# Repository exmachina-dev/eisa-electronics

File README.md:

```
____ _ ____ _    ____    ____ _    ____ ____ ___ ____ ____ _  _ _ ____ ____ 
|___ | [__  |    |__| __ |___ |    |___ |     |  |__/ |  | |\ | | |    [__  
|___ | ___] |___ |  |    |___ |___ |___ |___  |  |  \ |__| | \| | |___ ___] 
 
```

# Eisla electronics

This repo contains all necessary files to design and produce PCBs for the Eisla product range.

## File format and folder structure

Documentation files should be in PDF. Board image files can be in PNG or PDF.

PCB design files are in EAGLE Standard edition (7.4) file format.

The following are general rules to help maintain a consistent folder structure:

* All libraries are placed inside the shared libraries repository. It can be found
  on [Github](https://github.com/exmchina-dev/eagle-resources)

* One board for each project folder.  

* Mutiples revisions can be placed inside a subfolder. i.e. `ArmazCape/Rev A1`

* BOMs, partlists, spreadsheet should placed inside a `BOMs/` folder.  

* Documentations files are in `doc/` inside a project folder.

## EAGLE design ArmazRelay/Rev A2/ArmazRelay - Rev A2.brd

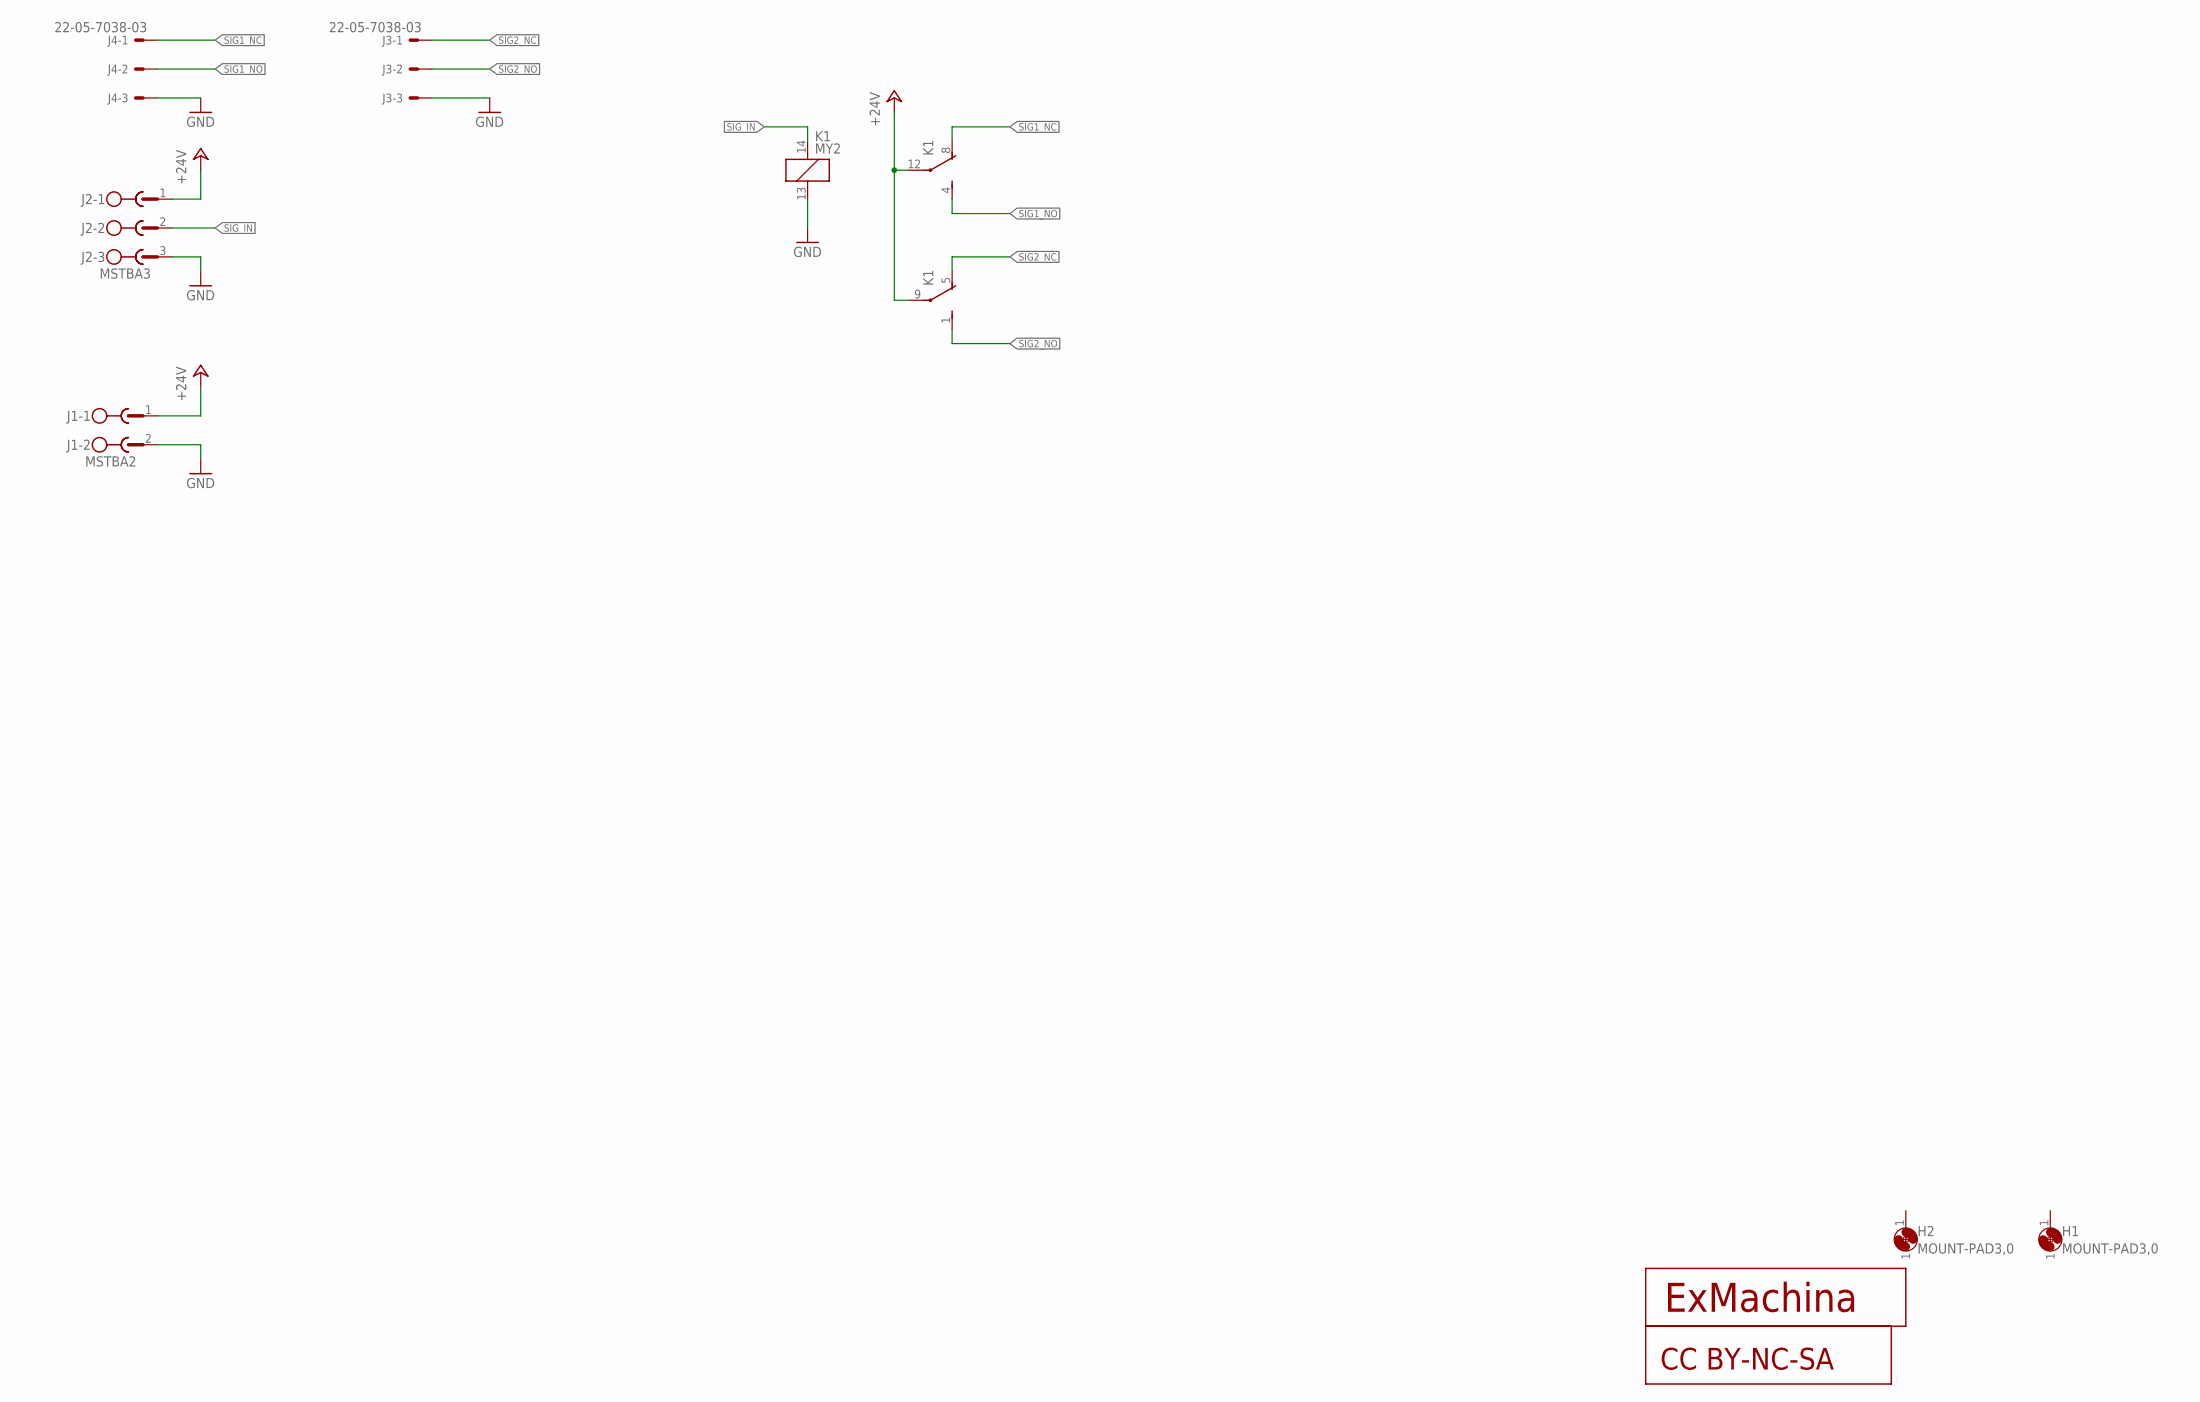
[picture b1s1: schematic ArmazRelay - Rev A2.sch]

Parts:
CC1: CC-BY-NC-SA
H1, H2: MOUNT-PAD3,0; P3,0
J1: MSTBA2
J2: MSTBA3
J3, J4: 22-05-7038-03; 7395-03
K1: MY2; PY08
T1: EXMACHINA-LOGO-NAME; EXM-LOGO-BASELINE

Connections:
+24V: J1.1, J2.1, K1.9 (C), K1.12 (C)
GND: J1.2, J2.3, J3.3, J4.3, K1.13 (COIL2)
SIG1_NC: J4.1, K1.8 (NO)
SIG1_NO: J4.2, K1.4 (NC)
SIG2_NC: J3.1, K1.5 (NO)
SIG2_NO: J3.2, K1.1 (NC)
SIG_IN: J2.2, K1.14 (COIL1)

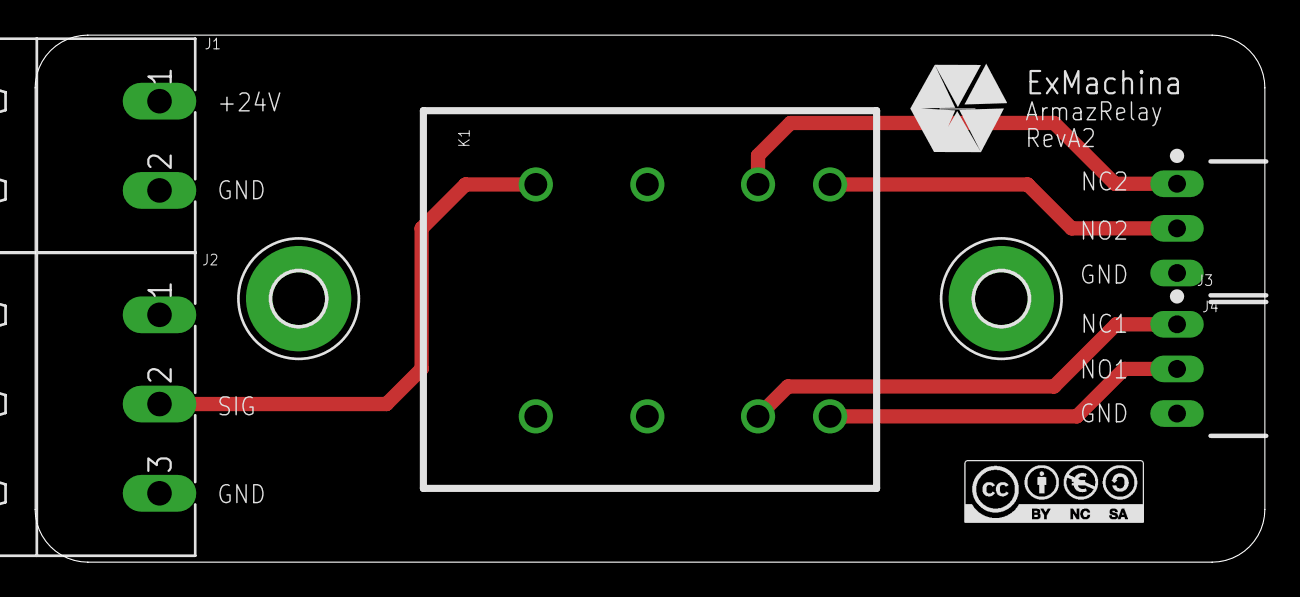
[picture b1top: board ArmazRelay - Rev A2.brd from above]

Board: 2 copper layers, 70.0 x 30.0 mm, 10 parts (0 on the bottom side), 7 nets.

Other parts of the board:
U$1: A4L-LOC

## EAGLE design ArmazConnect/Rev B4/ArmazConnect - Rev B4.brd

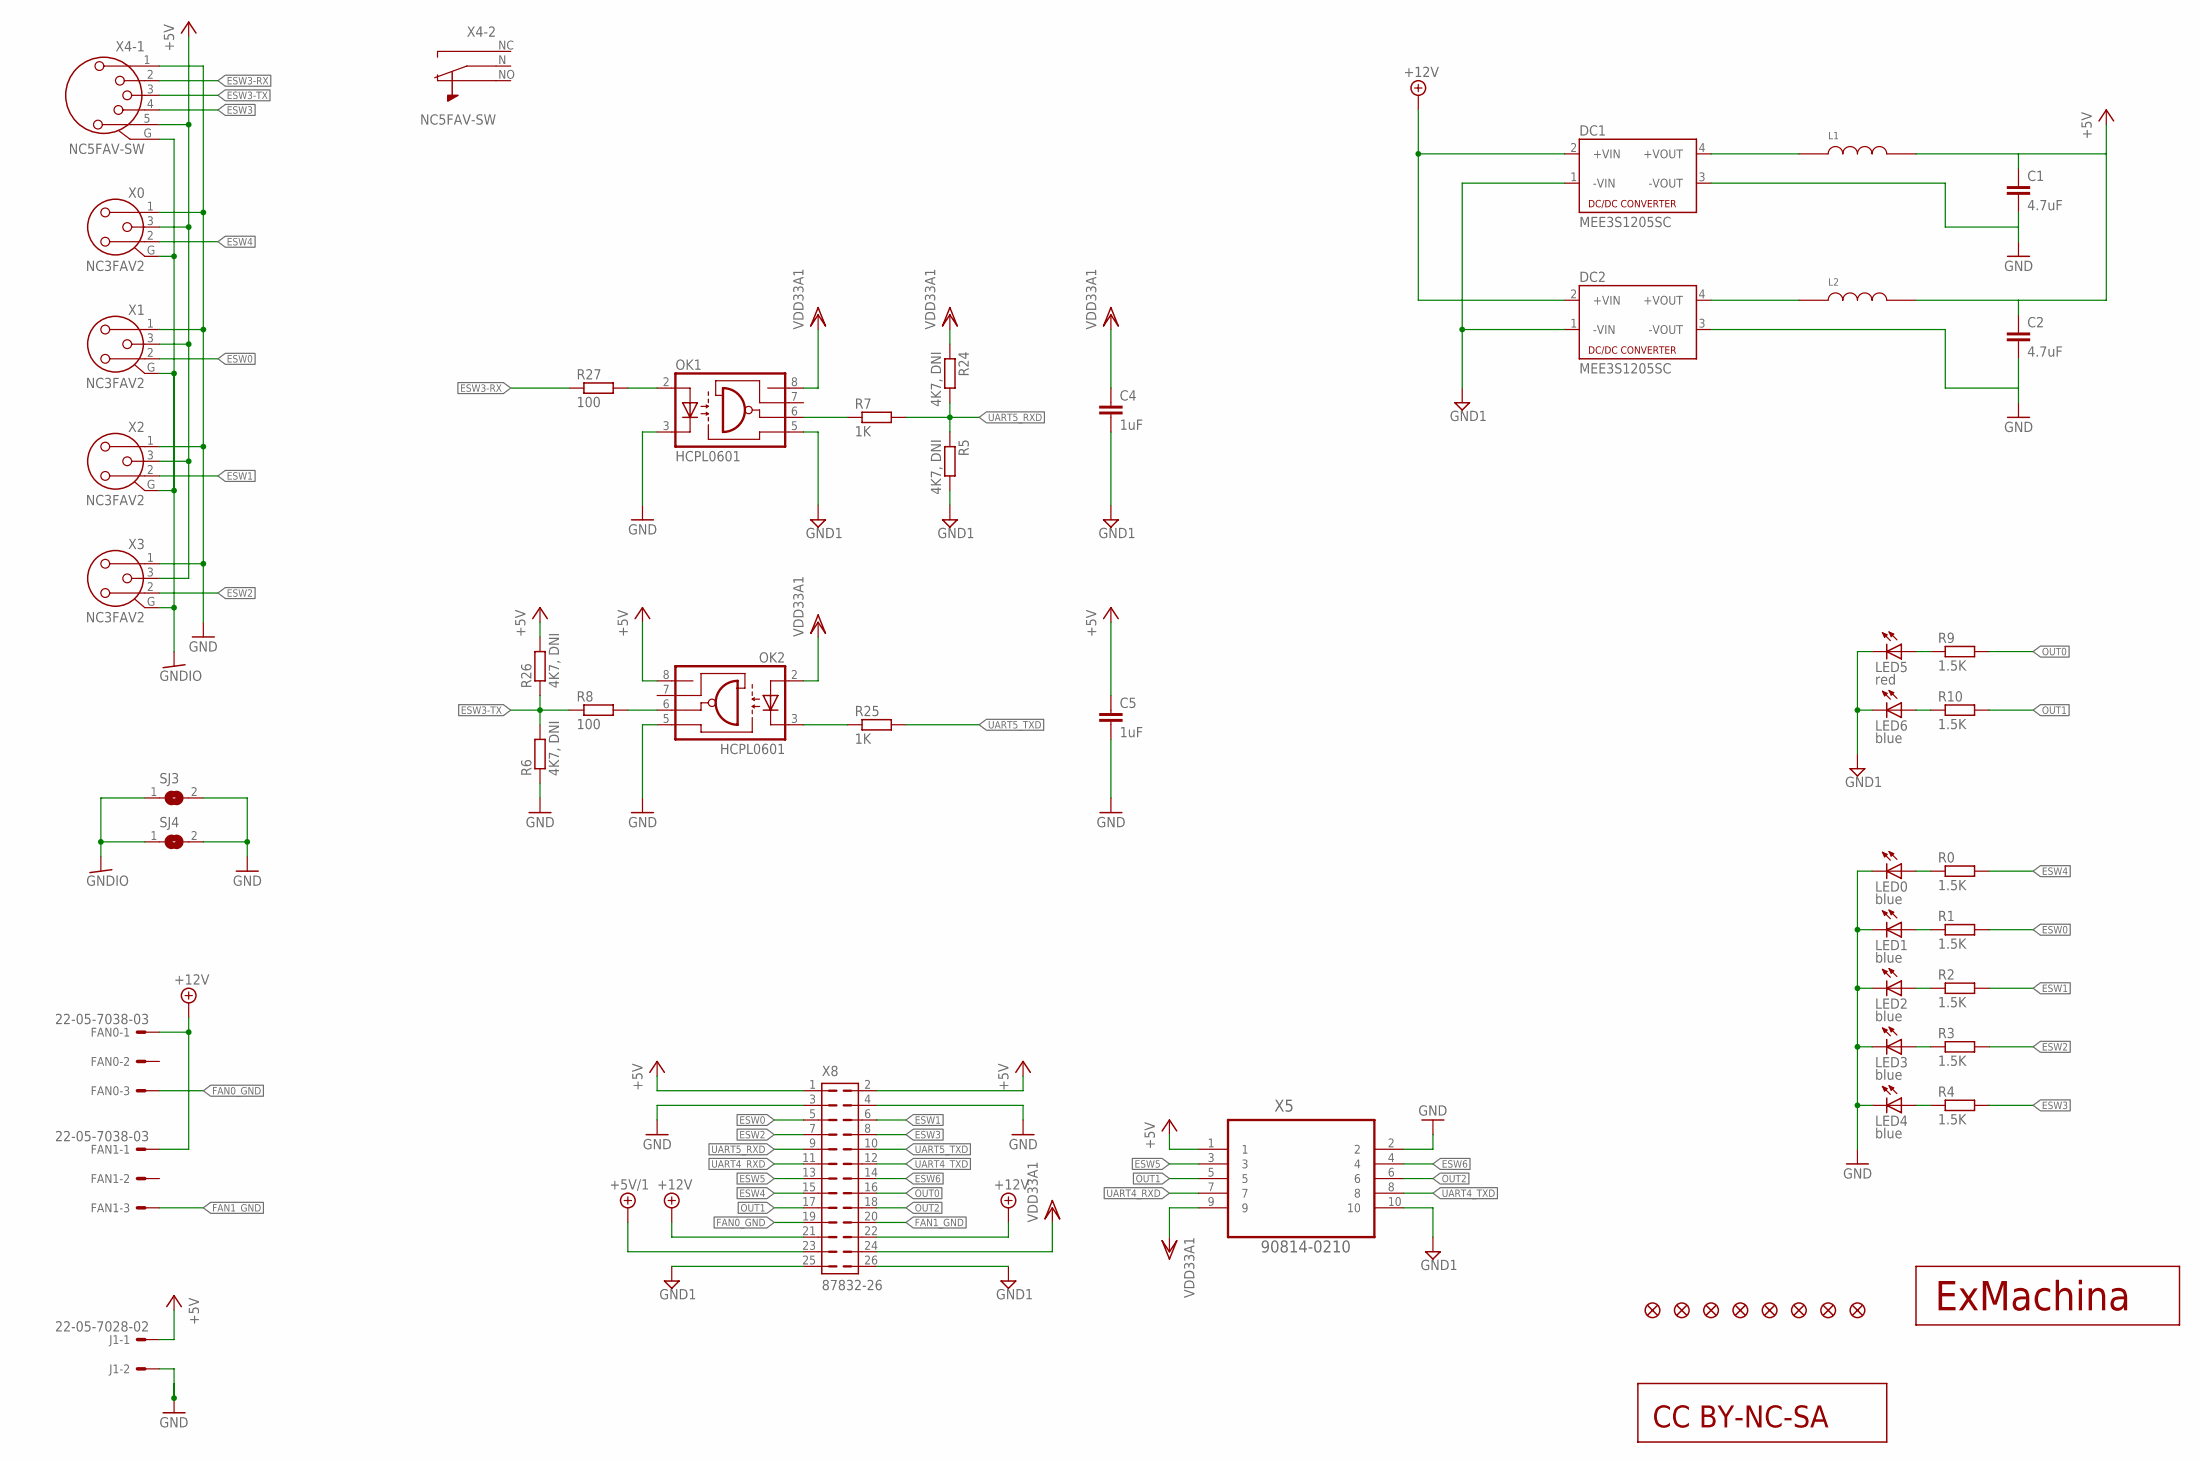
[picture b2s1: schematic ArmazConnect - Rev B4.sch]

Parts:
C1, C2: 4.7uF; C0603; MPN MC0603X475K6R3CT
C4, C5: 1uF; C0805; MPN MC0805F105Z500CT
CC1: CC-BY-NC-SA
DC1, DC2: MEE3S1205SC; MEE3; MPN MEE3S1205SC
FAN0, FAN1: 22-05-7038-03; 7395-03; MPN 22-05-7038
FI1, FI2, FI3, FI4, FI5, FI6, FI7, FI8: FIDUCIAL1X2; FIDUCIAL-1X2
J1: 22-05-7028-02; 7395-02
L1, L2: 84103C; 8200; MPN 744045100
LED0, LED1, LED2, LED3, LED4, LED6: blue; CHIP-LED0603; MPN OVS-0603
LED5: red; CHIP-LED0603; MPN OVS-0603
OK1, OK2: HCPL0601; SOIC08
R0, R1, R2, R3, R4, R9, R10: 1.5K; R0603; MPN MCMR06X1501FTL
R5, R6, R24, R26: 4K7, DNI; R0603; MPN MCMR04X3301FTL
R7, R25: 1K; R0603; MPN MCMR06X3300FTL
R8, R27: 100; R0603; MPN MCMR06X4701FTL
SJ3, SJ4: SJ
U$1: EXMACHINA-LOGO-NAME; EXM-LOGO-BASELINE
X0, X1, X2, X3: NC3FAV2; MPN NC3FAAV2
X4: NC5FAV-SW
X5: 90814-0210; MOLEX_90814-0210
X8: 87832-26; MPN 87832-2620

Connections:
+5V: C1.1, C2.1, C5.1, J1.1, L1.2, L2.2, OK2.8 (VCC), R26.2, X0.3, X1.3, X2.3, X3.3, X4.5, X5.1, X8.1, X8.2
+5V/1: X8.23
+12V: DC1.2 (+VIN), DC2.2 (+VIN), FAN0.1, FAN1.1, X8.21, X8.22
ESW0: R1.2, X1.2, X8.5
ESW1: R2.2, X2.2, X8.6
ESW2: R3.2, X3.2, X8.7
ESW3: R4.2, X4.4, X8.8
ESW3-RX: R27.1, X4.2
ESW3-TX: R6.2, R8.1, R26.1, X4.3
ESW4: R0.2, X0.2, X8.15
ESW5: X5.3, X8.13
ESW6: X5.4, X8.14
FAN0_GND: FAN0.3, X8.19
FAN1_GND: FAN1.3, X8.20
GND: C1.2, C2.2, C5.2, DC1.3 (-VOUT), DC2.3 (-VOUT), J1.2, LED0.C, LED1.C, LED2.C, LED3.C, LED4.C, OK1.3 (C), OK2.5 (GND), R6.1, SJ3.2, SJ4.2, X0.1, X1.1, X2.1, X3.1, X4.1, X5.2, X8.3, X8.4
GND1: C4.2, DC1.1 (-VIN), DC2.1 (-VIN), LED5.C, LED6.C, OK1.5 (GND), R5.2, X5.10, X8.25, X8.26
GNDIO: SJ3.1, SJ4.1, X0.G, X1.G, X2.G, X3.G, X4.G
unnamed: LED1.A, R1.1
unnamed: LED2.A, R2.1
unnamed: LED3.A, R3.1
unnamed: LED4.A, R4.1
unnamed: DC1.4 (+VOUT), L1.1
unnamed: OK1.2 (A), R27.2
unnamed: DC2.4 (+VOUT), L2.1
unnamed: OK2.6 (VO), R8.2
unnamed: LED5.A, R9.1
unnamed: OK1.6 (VO), R7.1
unnamed: LED6.A, R10.1
unnamed: LED0.A, R0.1
unnamed: OK2.3 (C), R25.1
OUT0: R9.2, X8.16
OUT1: R10.2, X5.5, X8.17
OUT2: X5.6, X8.18
UART4_RXD: X5.7, X8.11
UART4_TXD: X5.8, X8.12
UART5_RXD: R5.1, R7.2, R24.2, X8.9
UART5_TXD: R25.2, X8.10
VDD33A1: C4.1, OK1.8 (VCC), OK2.2 (A), R24.1, X5.9, X8.24

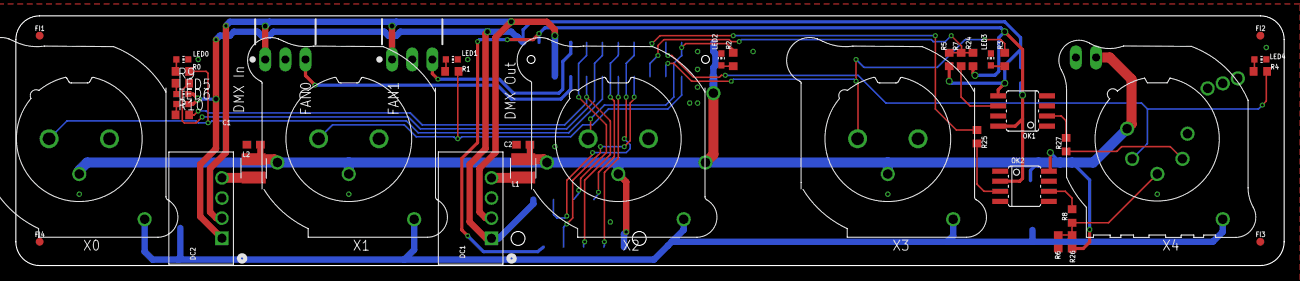
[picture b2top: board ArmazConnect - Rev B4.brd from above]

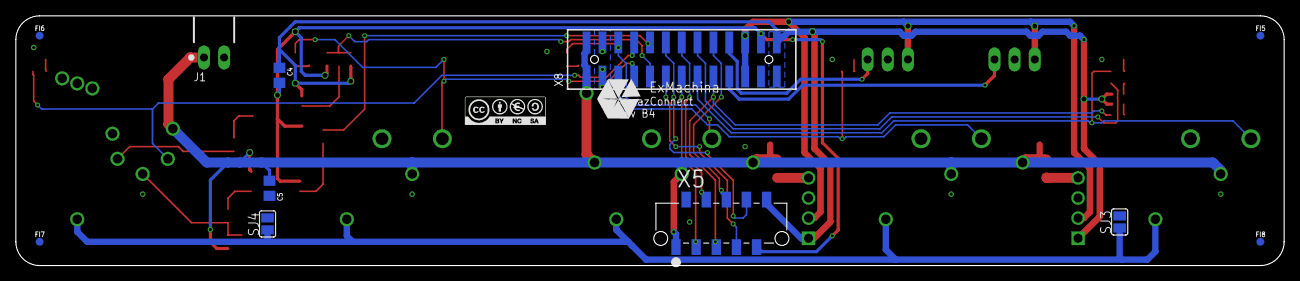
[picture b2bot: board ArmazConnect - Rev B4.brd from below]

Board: 2 copper layers, 160.0 x 31.5 mm, 54 parts (13 on the bottom side), 37 nets.

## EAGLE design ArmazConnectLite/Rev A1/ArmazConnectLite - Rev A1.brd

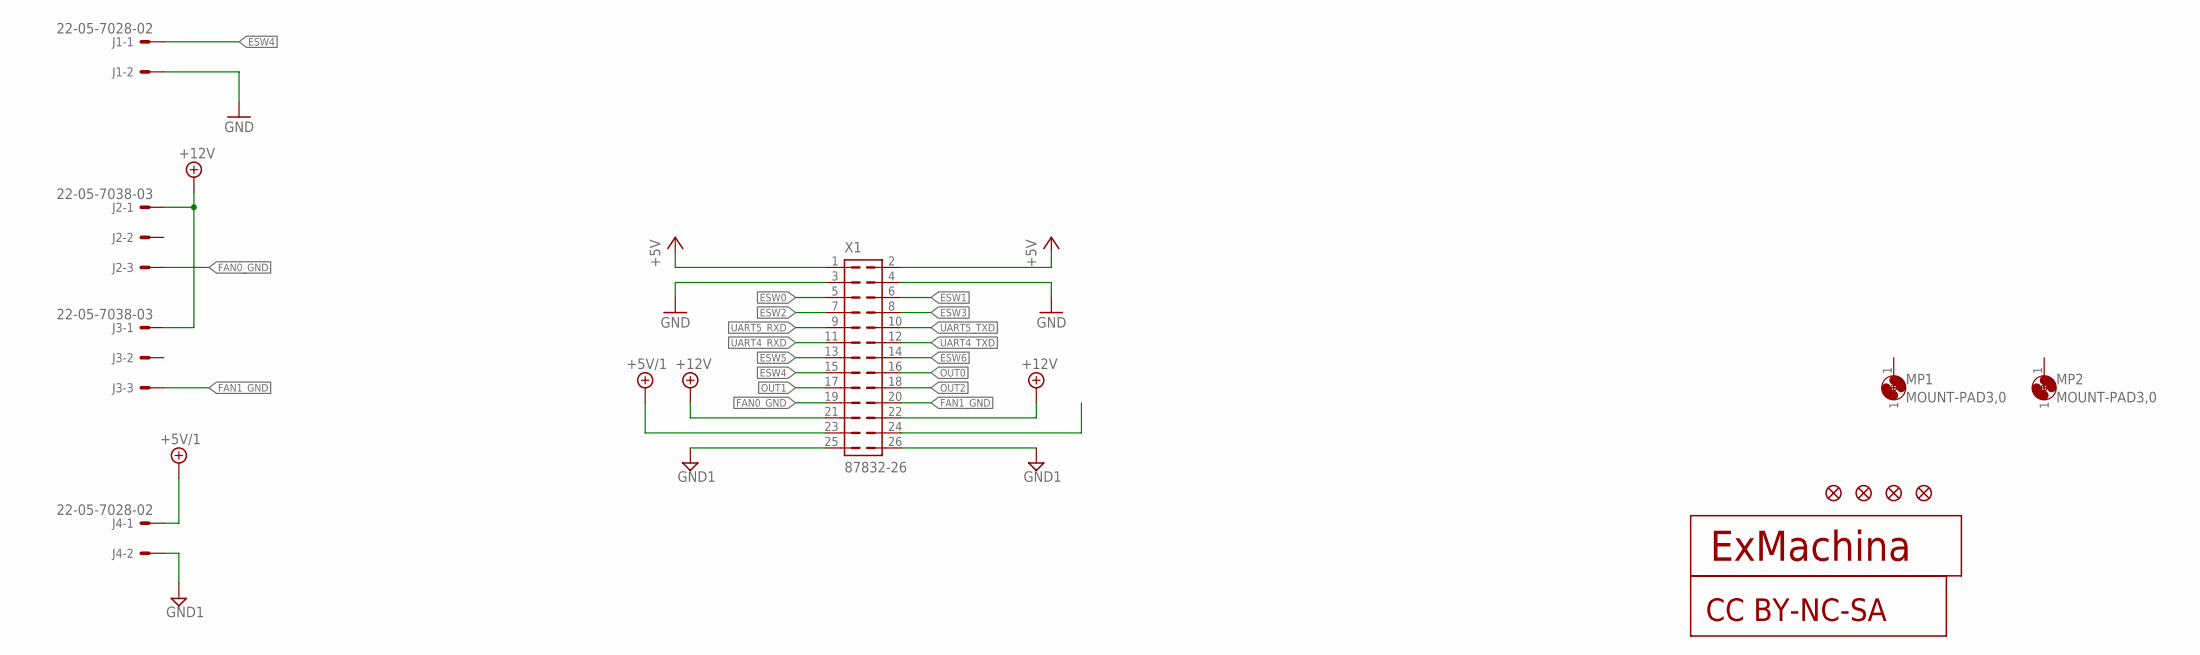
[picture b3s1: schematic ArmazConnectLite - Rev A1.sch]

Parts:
CC1: CC-BY-NC-SA
J1, J4: 22-05-7028-02; 7395-02
J2, J3: 22-05-7038-03; 7395-03; MPN 22-05-7038
JP1, JP2, JP3, JP4: FIDUCIAL1X2; FIDUCIAL-1X2
MP1, MP2: MOUNT-PAD3,0; P3,0
T1: EXMACHINA-LOGO-NAME; EXM-LOGO-BASELINE
X1: 87832-26; MPN 87832-2620

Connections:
+5V: X1.1, X1.2
+5V/1: J4.1, X1.23
+12V: J2.1, J3.1, X1.21, X1.22
ESW0: X1.5
ESW1: X1.6
ESW2: X1.7
ESW3: X1.8
ESW4: J1.1, X1.15
ESW5: X1.13
ESW6: X1.14
FAN0_GND: J2.3, X1.19
FAN1_GND: J3.3, X1.20
GND: J1.2, X1.3, X1.4
GND1: J4.2, X1.25, X1.26
OUT0: X1.16
OUT1: X1.17
OUT2: X1.18
UART4_RXD: X1.11
UART4_TXD: X1.12
UART5_RXD: X1.9
UART5_TXD: X1.10

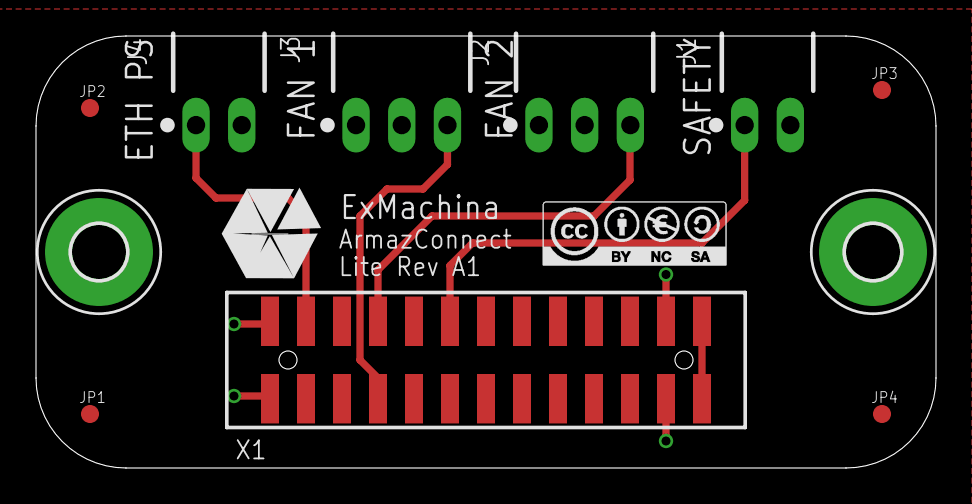
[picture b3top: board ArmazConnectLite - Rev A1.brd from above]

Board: 2 copper layers, 50.0 x 24.0 mm, 14 parts (0 on the bottom side), 8 nets.

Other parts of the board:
U$2: A4L-LOC

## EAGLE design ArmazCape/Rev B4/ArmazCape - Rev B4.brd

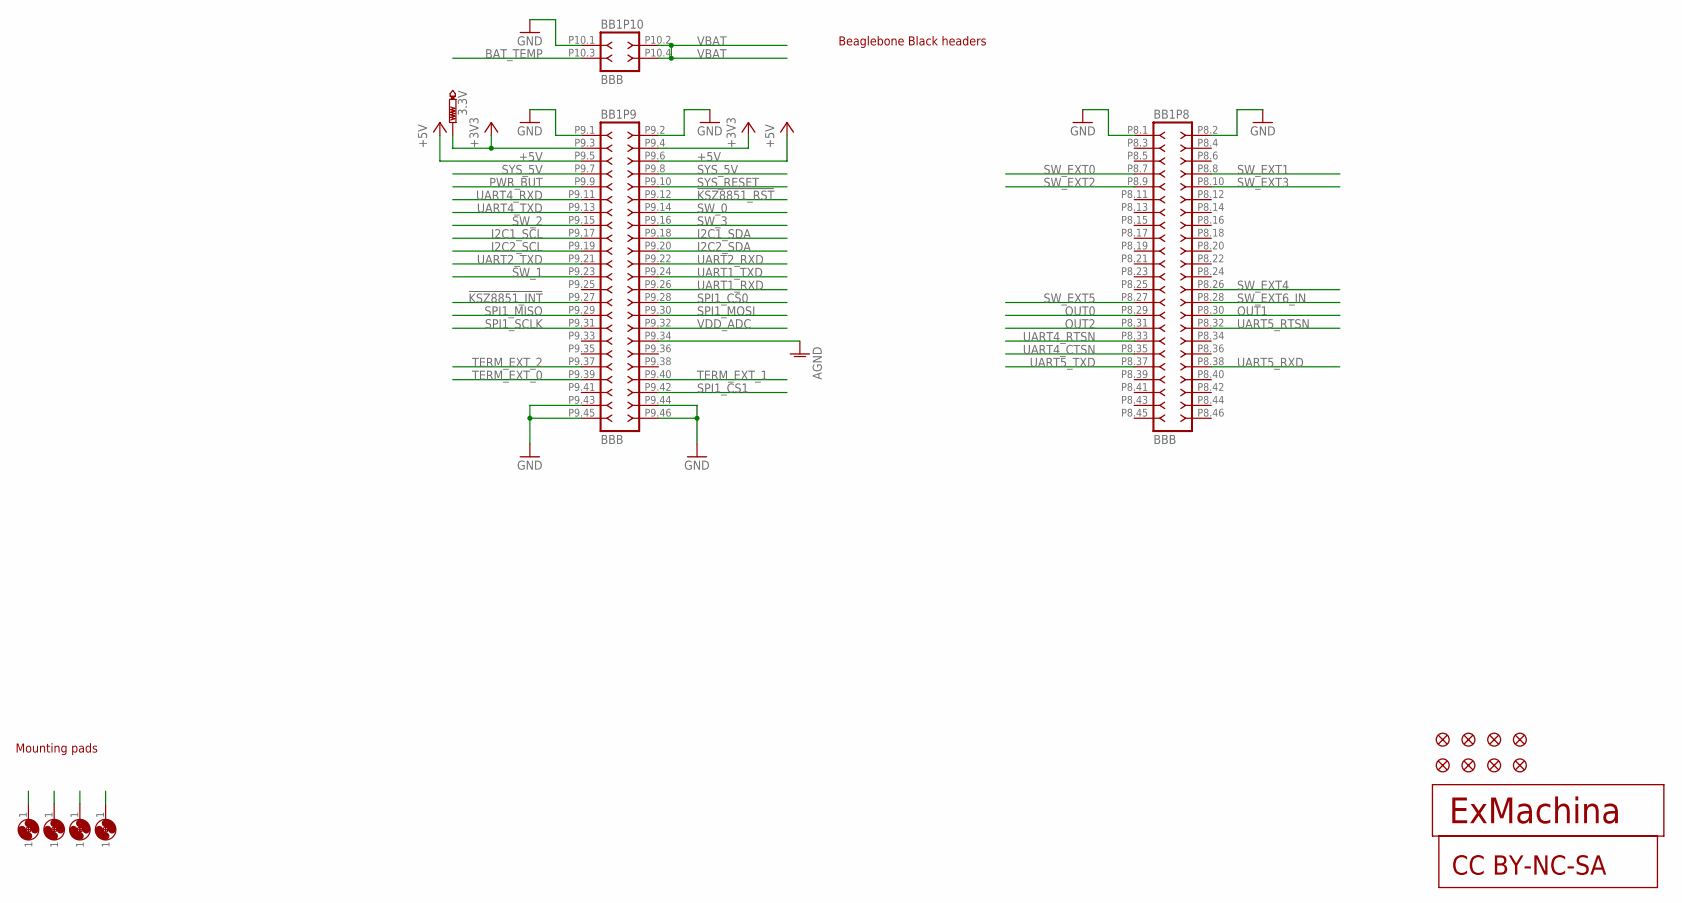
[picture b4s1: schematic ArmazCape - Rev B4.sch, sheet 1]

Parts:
3.3V: PTR1TP11R; TP11R
BB1: BBB
FI1, FI2, FI3, FI4, FI5, FI6, FI7, FI8: FIDUCIAL1X2; FIDUCIAL-1X2
H1, H2, H3, H4: MOUNT-PAD3,0; P3,0
U$1: EXMACHINA-LOGO-NAME; EXM-LOGO-BASELINE
U$7: CC-BY-NC-SA

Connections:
!KSZ8851_INT: BB1.P9.27 (27); also elsewhere on the board
!KSZ8851_RST: BB1.P9.12 (12); also elsewhere on the board
+3V3: 3.3V.TP, BB1.P9.3 (3), BB1.P9.4 (4); also elsewhere on the board
+5V: BB1.P9.5 (5), BB1.P9.6 (6); also elsewhere on the board
AGND: BB1.P9.34 (34)
BAT_TEMP: BB1.P10.3 (3); also elsewhere on the board
GND: BB1.P8.1 (1), BB1.P8.2 (2), BB1.P9.1 (1), BB1.P9.2 (2), BB1.P9.43 (43), BB1.P9.44 (44), BB1.P9.45 (45), BB1.P9.46 (46), BB1.P10.1 (1); also elsewhere on the board
I2C1_SCL: BB1.P9.17 (17)
I2C1_SDA: BB1.P9.18 (18)
I2C2_SCL: BB1.P9.19 (19); also elsewhere on the board
I2C2_SDA: BB1.P9.20 (20); also elsewhere on the board
OUT0: BB1.P8.29 (29); also elsewhere on the board
OUT1: BB1.P8.30 (30); also elsewhere on the board
OUT2: BB1.P8.31 (31); also elsewhere on the board
PWR_BUT: BB1.P9.9 (9)
SPI1_CS0: BB1.P9.28 (28); also elsewhere on the board
SPI1_CS1: BB1.P9.42 (42)
SPI1_MISO: BB1.P9.29 (29); also elsewhere on the board
SPI1_MOSI: BB1.P9.30 (30); also elsewhere on the board
SPI1_SCLK: BB1.P9.31 (31); also elsewhere on the board
SW_0: BB1.P9.14 (14); also elsewhere on the board
SW_1: BB1.P9.23 (23); also elsewhere on the board
SW_2: BB1.P9.15 (15); also elsewhere on the board
SW_3: BB1.P9.16 (16); also elsewhere on the board
SW_EXT0: BB1.P8.7 (7); also elsewhere on the board
SW_EXT1: BB1.P8.8 (8); also elsewhere on the board
SW_EXT2: BB1.P8.9 (9); also elsewhere on the board
SW_EXT3: BB1.P8.10 (10); also elsewhere on the board
SW_EXT4: BB1.P8.26 (26); also elsewhere on the board
SW_EXT5: BB1.P8.27 (27); also elsewhere on the board
SW_EXT6_IN: BB1.P8.28 (28); also elsewhere on the board
SYS_5V: BB1.P9.7 (7), BB1.P9.8 (8); also elsewhere on the board
SYS_RESET: BB1.P9.10 (10)
TERM_EXT_0: BB1.P9.39 (39); also elsewhere on the board
TERM_EXT_1: BB1.P9.40 (40); also elsewhere on the board
TERM_EXT_2: BB1.P9.37 (37); also elsewhere on the board
UART1_RXD: BB1.P9.26 (26)
UART1_TXD: BB1.P9.24 (24)
UART2_RXD: BB1.P9.22 (22)
UART2_TXD: BB1.P9.21 (21)
UART4_CTSN: BB1.P8.35 (35)
UART4_RTSN: BB1.P8.33 (33)
UART4_RXD: BB1.P9.11 (11); also elsewhere on the board
UART4_TXD: BB1.P9.13 (13); also elsewhere on the board
UART5_RTSN: BB1.P8.32 (32)
UART5_RXD: BB1.P8.38 (38); also elsewhere on the board
UART5_TXD: BB1.P8.37 (37); also elsewhere on the board
VBAT: BB1.P10.2 (2), BB1.P10.4 (4); also elsewhere on the board
VDD_ADC: BB1.P9.32 (32); also elsewhere on the board

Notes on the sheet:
Beaglebone Black headers
Mounting pads

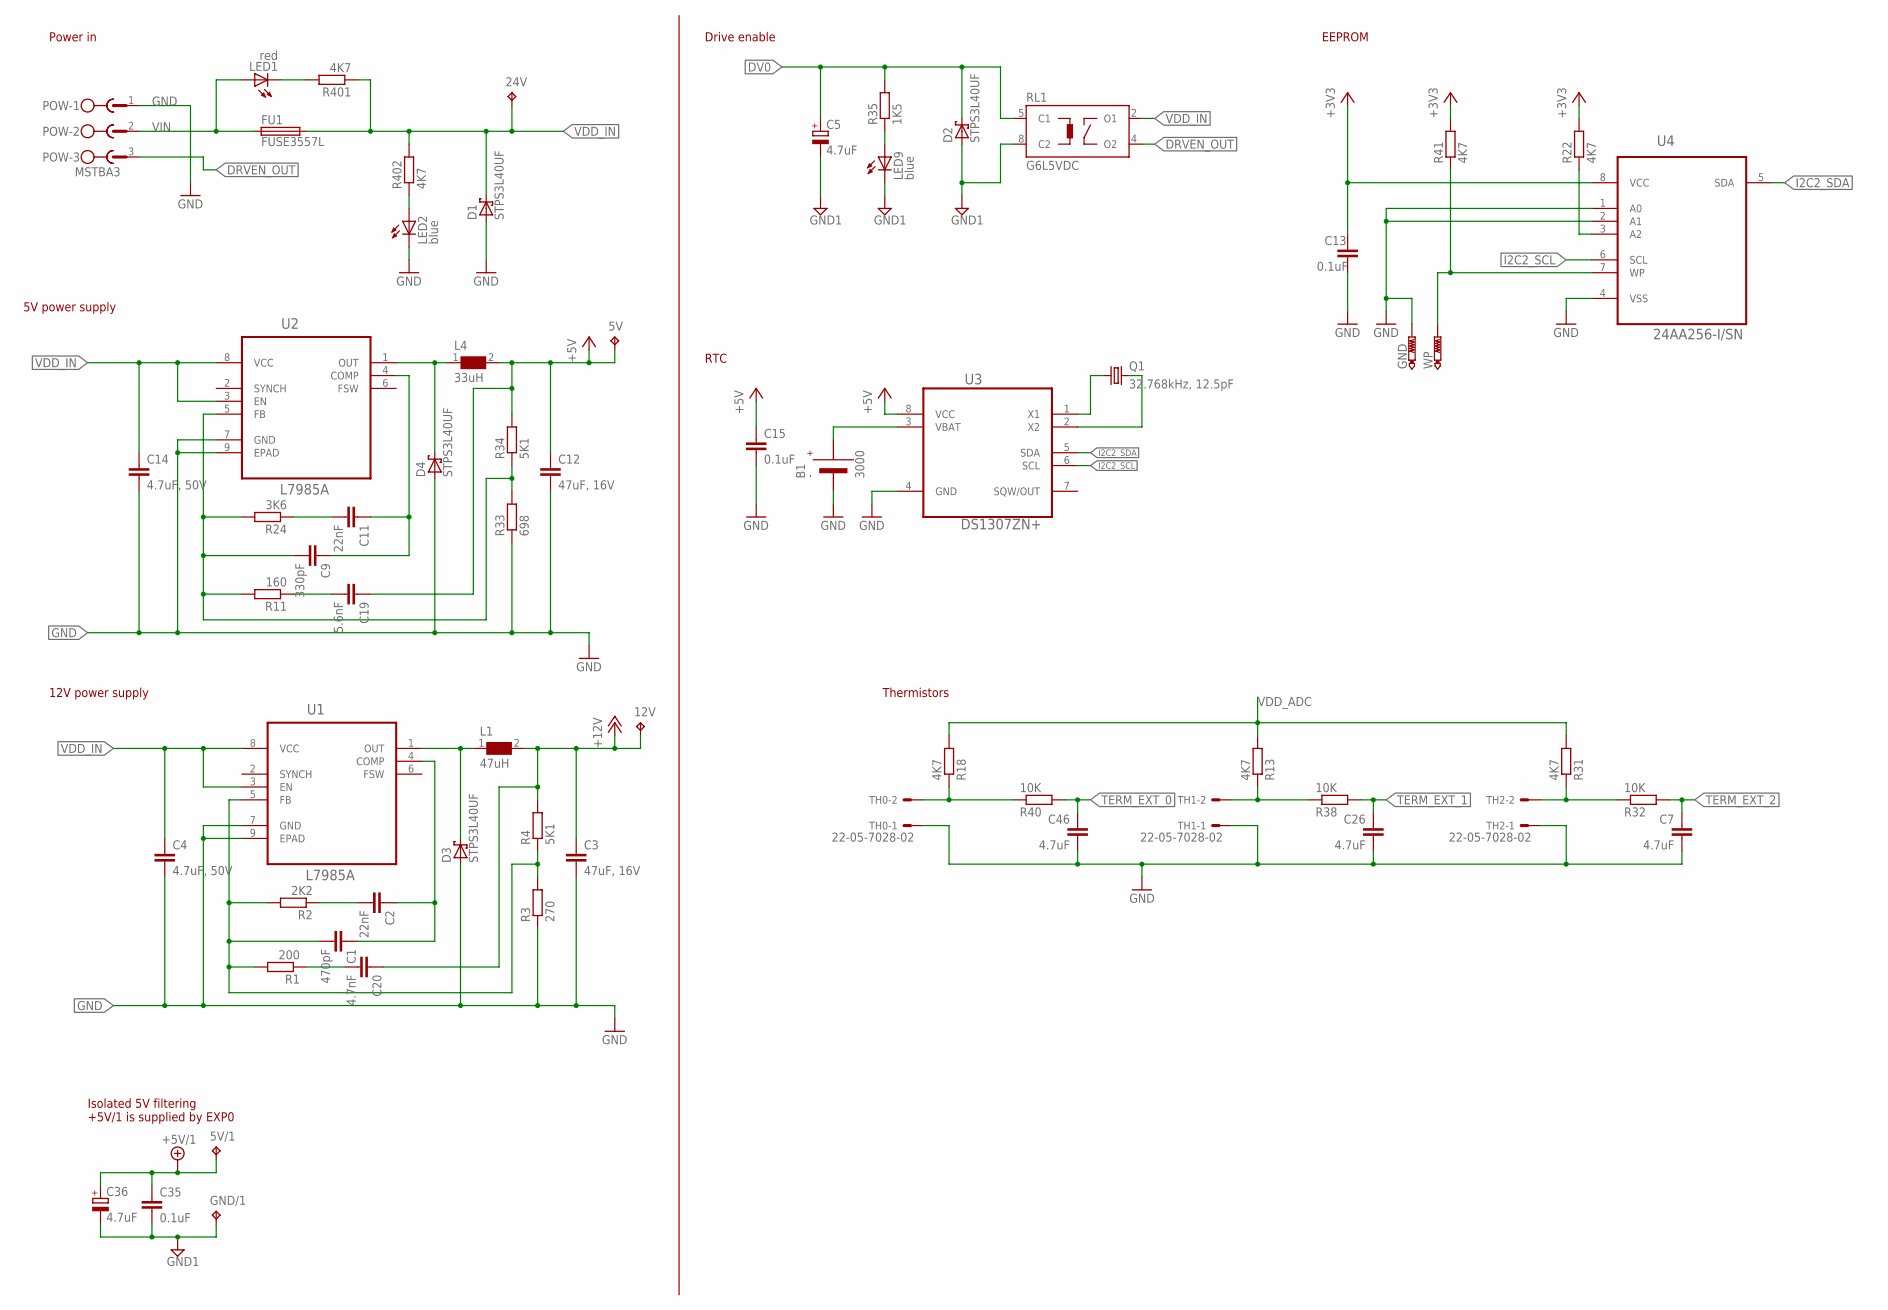
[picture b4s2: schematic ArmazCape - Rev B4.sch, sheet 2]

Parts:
5V, 5V/1, 12V, 24V: TPB1,27; B1,27
B1: 3000; MPN 3000
C1: 470pF; C0603; MPN GRM1885C1H471JA01D
C2, C11: 22nF; C0603; MPN GRM188R71H223KA01D
C3, C12: 47uF, 16V; C1210; MPN GRM32ER61C476KE15K
C4, C14: 4.7uF, 50V; C1210; MPN GCM32ER71H475KA55L
C5, C36: 4.7uF; CT3216; MPN T491A475K010AT
C7, C26, C46: 4.7uF; C0603; MPN GRM188R60J475KE19D
C9: 330pF; C0603; MPN GRM1885C1H331JA01D
C13, C15, C35: 0.1uF; C0603; MPN GRM188R71H104KA93D
C19: 5.6nF; C0603; MPN C0603C562J5GACTU
C20: 4.7nF; C0603; MPN GRM188R71H472KA01D
D1, D2, D3, D4: STPS3L40UF; SMB
FU1: FUSE3557L; 3557-LITTLE; MPN 3557
GND: PTR1TP11SQ; TP11SQ
GND/1: TPB1,27; B1,27
L1: 47uH; WE-PD_1260/1245/1280/1210
L4: 33uH; WE-PD_1260/1245/1280/1210
LED1: red; CHIP-LED0603; MPN OVS-0608
LED2, LED9: blue; CHIP-LED0603; MPN OVS-0603
POW: MSTBA3
Q1: 32.768kHz, 12.5pF; ABS07; MPN ABS06-32.768KHZ-T
R1: 200; R0603; MPN RC0603FR-07200RL
R2: 2K2; R0603; MPN RC0603FR-072K2L
R3: 270; R0603; MPN RC0603FR-07270RL
R4, R34: 5K1; R0603; MPN RC0603FR-075K1L
R11: 160; R0603; MPN RC0603FR-07160RL
R13, R18, R22, R31, R41, R401, R402: 4K7; R0603; MPN RC0603FR-074K7L
R24: 3K6; R0603; MPN RC0603FR-073K6L
R32, R38, R40: 10K; R0603; MPN RC0603FR-0710KL
R33: 698; R0603; MPN RC0603FR-07698RL
R35: 1K5; R0603; MPN RC0603FR-071K5L
RL1: G6L5VDC; G6L-1F; MPN G6L-1F DC5
TH0, TH1, TH2: 22-05-7028-02; 7395-02; MPN 22-05-7028
U1, U2: L7985A; SOIC127P600X170-9N
U3: DS1307ZN+; MAXIM_SOIC127P600X175-8N; MPN DS1307N+
U4: 24AA256-I/SN; MICROCHIP_BY_ELEMENT14_BATCH_1_SOIC127P600X175-8N
WP: PTR1TP11R; TP11R

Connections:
+3V3: C13.1, R22.2, R41.2, U4.8 (VCC); also elsewhere on the board
+5V: 5V.TP, C12.1, C15.1, C19.1, L4.2, R34.2, U3.8 (VCC); also elsewhere on the board
+5V/1: 5V/1.TP, C35.1, C36.+; also elsewhere on the board
+12V: 12V.TP, C3.1, C20.1, L1.2, R4.2; also elsewhere on the board
DRVEN_OUT: POW.3, RL1.4 (O2)
DV0: C5.+, D2.C, R35.2, RL1.5 (C1); also elsewhere on the board
GND: B1.- (VBAT-), C3.2, C4.2, C7.2, C12.2, C13.2, C14.2, C15.2, C26.2, C46.2, D1.A, D3.A, D4.A, GND.TP, LED2.C, POW.1, R3.1, R33.1, TH0.1, TH1.1, TH2.1, U1.7 (GND), U1.9 (EPAD), U2.7 (GND), U2.9 (EPAD), U3.4 (GND), U4.1 (A0), U4.2 (A1), U4.4 (VSS); also elsewhere on the board
GND1: C5.-, C35.2, C36.-, D2.A, GND/1.TP, LED9.C, RL1.8 (C2); also elsewhere on the board
I2C2_SCL: U3.6 (SCL), U4.6 (SCL); also elsewhere on the board
I2C2_SDA: U3.5 (SDA), U4.5 (SDA); also elsewhere on the board
unnamed: C1.2, R1.2, R2.2, R3.2, R4.1, U1.5 (FB)
unnamed: C2.2, R2.1
unnamed: C1.1, C2.1, U1.4 (COMP)
unnamed: LED9.A, R35.1
unnamed: LED1.C, R401.2
unnamed: D4.C, L4.1, U2.1 (OUT)
unnamed: C9.2, R11.2, R24.2, R33.2, R34.1, U2.5 (FB)
unnamed: Q1.1, U3.1 (X1)
unnamed: R31.1, R32.1, TH2.2
unnamed: Q1.2, U3.2 (X2)
unnamed: C11.2, R24.1
unnamed: C9.1, C11.1, U2.4 (COMP)
unnamed: D3.C, L1.1, U1.1 (OUT)
unnamed: C19.2, R11.1
unnamed: C20.2, R1.1
unnamed: R41.1, U4.7 (WP), WP.TP
unnamed: R22.1, U4.3 (A2)
unnamed: LED2.A, R402.1
unnamed: R13.1, R38.1, TH1.2
unnamed: R18.1, R40.1, TH0.2
TERM_EXT_0: C46.1, R40.2; also elsewhere on the board
TERM_EXT_1: C26.1, R38.2; also elsewhere on the board
TERM_EXT_2: C7.1, R32.2; also elsewhere on the board
VBAT+: B1.+1 (VBAT+), B1.+2 (VBAT+), U3.3 (VBAT)
VDD_ADC: R13.2, R18.2, R31.2; also elsewhere on the board
VDD_IN: 24V.TP, C4.1, C14.1, D1.C, FU1.3 (2), FU1.4 (2), R401.1, R402.2, RL1.2 (O1), U1.3 (EN), U1.8 (VCC), U2.3 (EN), U2.8 (VCC)
VIN: FU1.1, FU1.2 (1), LED1.A, POW.2

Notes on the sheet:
Power in
5V power supply
12V power supply
Drive enable
EEPROM
RTC
Isolated 5V filtering +5V/1 is supplied by EXP0
Thermistors

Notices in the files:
ArmazCape/Rev B4/ArmazCape - Rev B4.brd:
Creatives Commons
CC BY-NC-SA
parts and their libraries:
COPYRIGHT: Copyright (C) 2015 Accelerated Designs. All rights reserved
